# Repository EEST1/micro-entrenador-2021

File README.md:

# micro-entrenador-2021
Una placa de entrenamiento para conectar en arduino NANO, realizada por los profesores de la EEST1

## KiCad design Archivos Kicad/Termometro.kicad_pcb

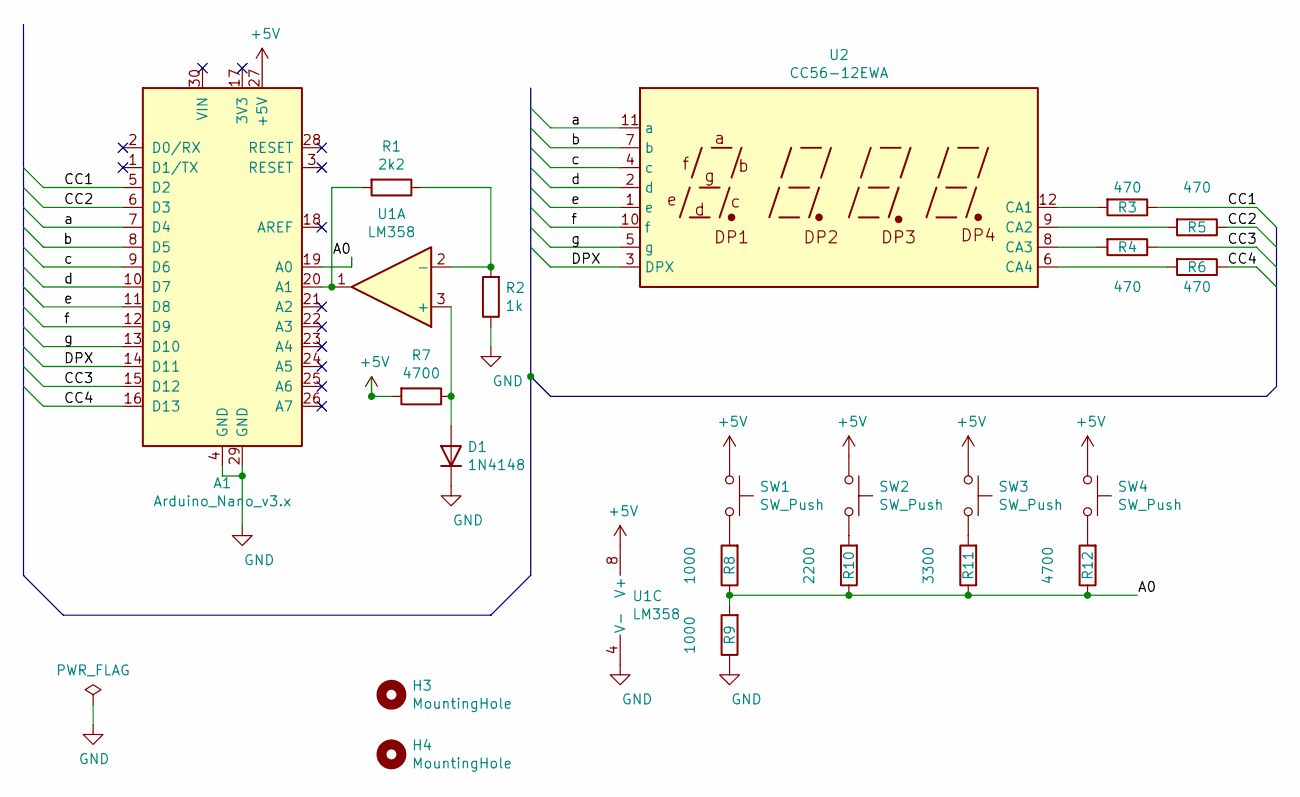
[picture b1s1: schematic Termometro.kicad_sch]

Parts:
A1: Arduino_Nano_v3.x; Arduino_Nano_WithMountingHoles
D1: 1N4148; D_DO-35_SOD27_P7.62mm_Horizontal
H3, H4: MountingHole; MountingHole_3.2mm_M3
R1: 2k2; R_Axial_DIN0207_L6.3mm_D2.5mm_P10.16mm_Horizontal
R2: 1k; R_Axial_DIN0207_L6.3mm_D2.5mm_P10.16mm_Horizontal
R3, R4, R5, R6: 470; R_Axial_DIN0207_L6.3mm_D2.5mm_P10.16mm_Horizontal
R7, R12: 4700; R_Axial_DIN0207_L6.3mm_D2.5mm_P10.16mm_Horizontal
R8, R9: 1000; R_Axial_DIN0207_L6.3mm_D2.5mm_P10.16mm_Horizontal
R10: 2200; R_Axial_DIN0207_L6.3mm_D2.5mm_P10.16mm_Horizontal
R11: 3300; R_Axial_DIN0207_L6.3mm_D2.5mm_P10.16mm_Horizontal
SW1, SW2, SW3, SW4: SW_Push; SW_PUSH_6mm_h5mm
U1: LM358; DIP-8_W7.62mm_LongPads
U2: CC56-12EWA; CA56-12EWA

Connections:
+5V: A1.27 (+5V), R7.2, SW1.1, SW2.1, SW3.1, SW4.1, U1.8 (V+)
/A0: A1.19 (A0), R8.1, R9.2, R10.1, R11.1, R12.1
/CC1: A1.5 (D2), R3.1
/CC2: A1.6 (D3), R5.1
/CC3: A1.15 (D12), R4.1
/CC4: A1.16 (D13), R6.1
/DPX: A1.14 (D11), U2.3 (DPX)
/a: A1.7 (D4), U2.11 (a)
/b: A1.8 (D5), U2.7 (b)
/c: A1.9 (D6), U2.4 (c)
/d: A1.10 (D7), U2.2 (d)
/e: A1.11 (D8), U2.1 (e)
/f: A1.12 (D9), U2.10 (f)
/g: A1.13 (D10), U2.5 (g)
GND: A1.4 (GND), A1.29 (GND), D1.1 (K), R2.1, R9.1, U1.4 (V-)
unnamed: A1.20 (A1), R1.2, U1.1
unnamed: D1.2 (A), R7.1, U1.3 (+)
unnamed: R1.1, R2.2, U1.2 (-)
unnamed: R3.2, U2.12 (CA1)
unnamed: R4.2, U2.8 (CA3)
unnamed: R5.2, U2.9 (CA2)
unnamed: R6.2, U2.6 (CA4)
unnamed: R8.2, SW1.2
unnamed: R10.2, SW2.2
unnamed: R11.2, SW3.2
unnamed: R12.2, SW4.2

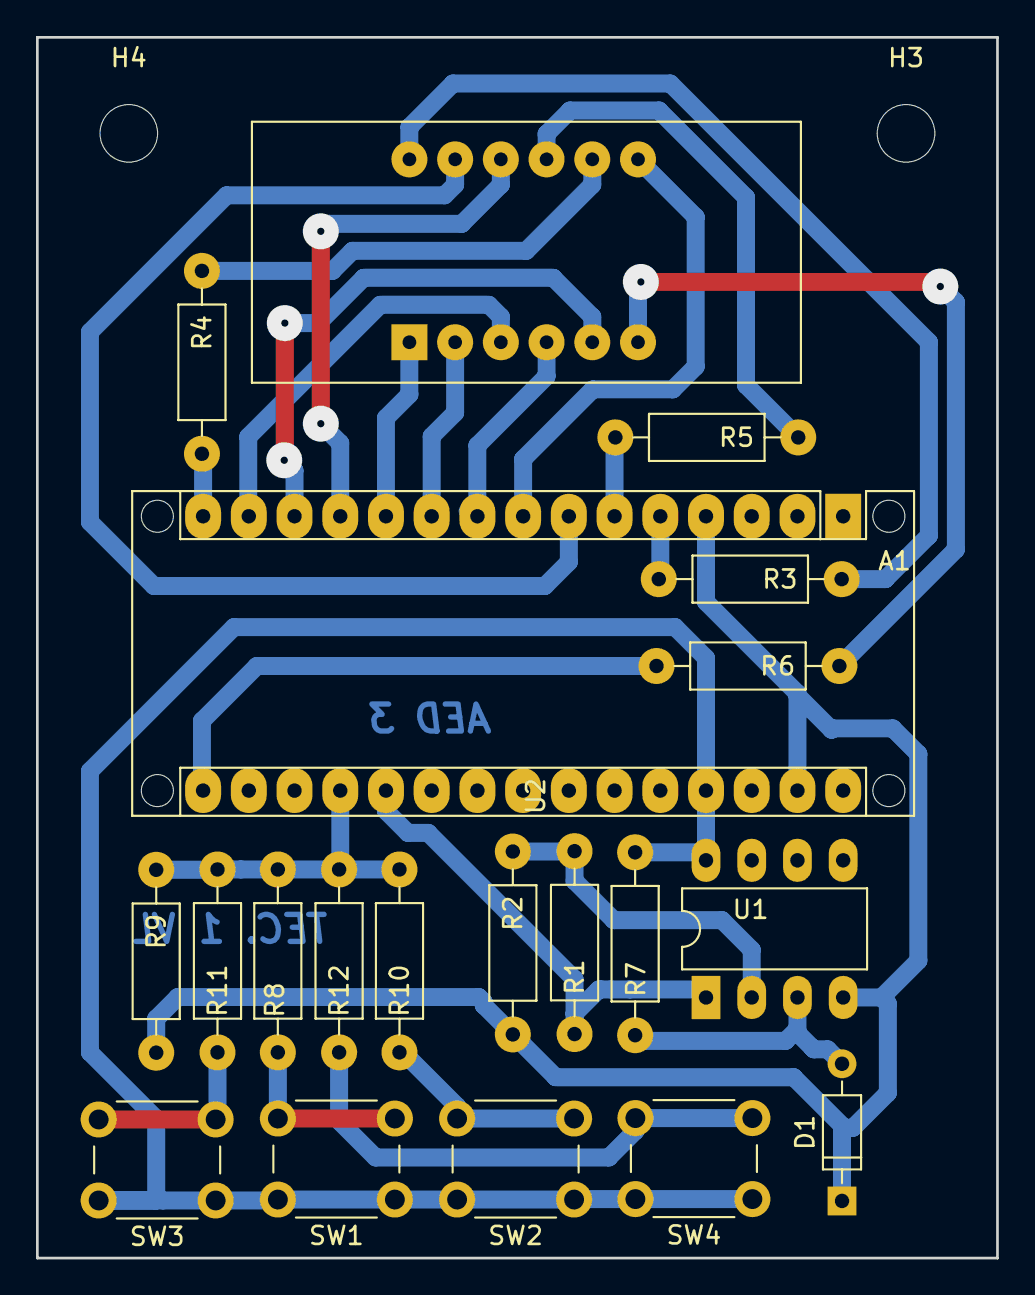
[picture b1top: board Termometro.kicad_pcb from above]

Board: 2 copper layers, 53.3 x 67.8 mm, 22 parts (0 on the bottom side), 26 nets.

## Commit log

2021-08-18 Primer commit
2021-11-11 Docs-Datasheet/microentrenador-2021-v1.pdf
2021-11-11 subiendo documento de el esquematico y pcb
2021-11-11 correccion del pdf
2022-02-18 modified: Archivos Kicad/Termometro.kicad_pcb Untracked files: Archivos FREECad/desktop.ini Archivos Kicad/LibreriaCustumLemos.pretty/desktop.ini Archivos Kicad/Termometro-backups/ Archivos Kicad/Ter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
2022-03-09 Please enter the commit message for your changes. Lines starting with '#' will be ignored, and an empty message aborts the commit.
    On branch main
    Your branch is up to date with 'origin/main'.
    Changes to be committed:
    new file: LibreriaCustumLemos.pretty/desktop.ini
    new file: Termometro-backups/Termometro-2022-02-16_182650.zip
    new file: Termometro-backups/Termometro-2022-02-17_154953.zip
2022-03-09 correccion del board
